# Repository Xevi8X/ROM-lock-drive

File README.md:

# ROM-lock-drive

This project is my intermediate engineering project (VI semester, Robotics, Faculty of Power and Aeronautical Engineering, WUT)

3D CAD models: https://grabcad.com/library/rom-lock-drive-1

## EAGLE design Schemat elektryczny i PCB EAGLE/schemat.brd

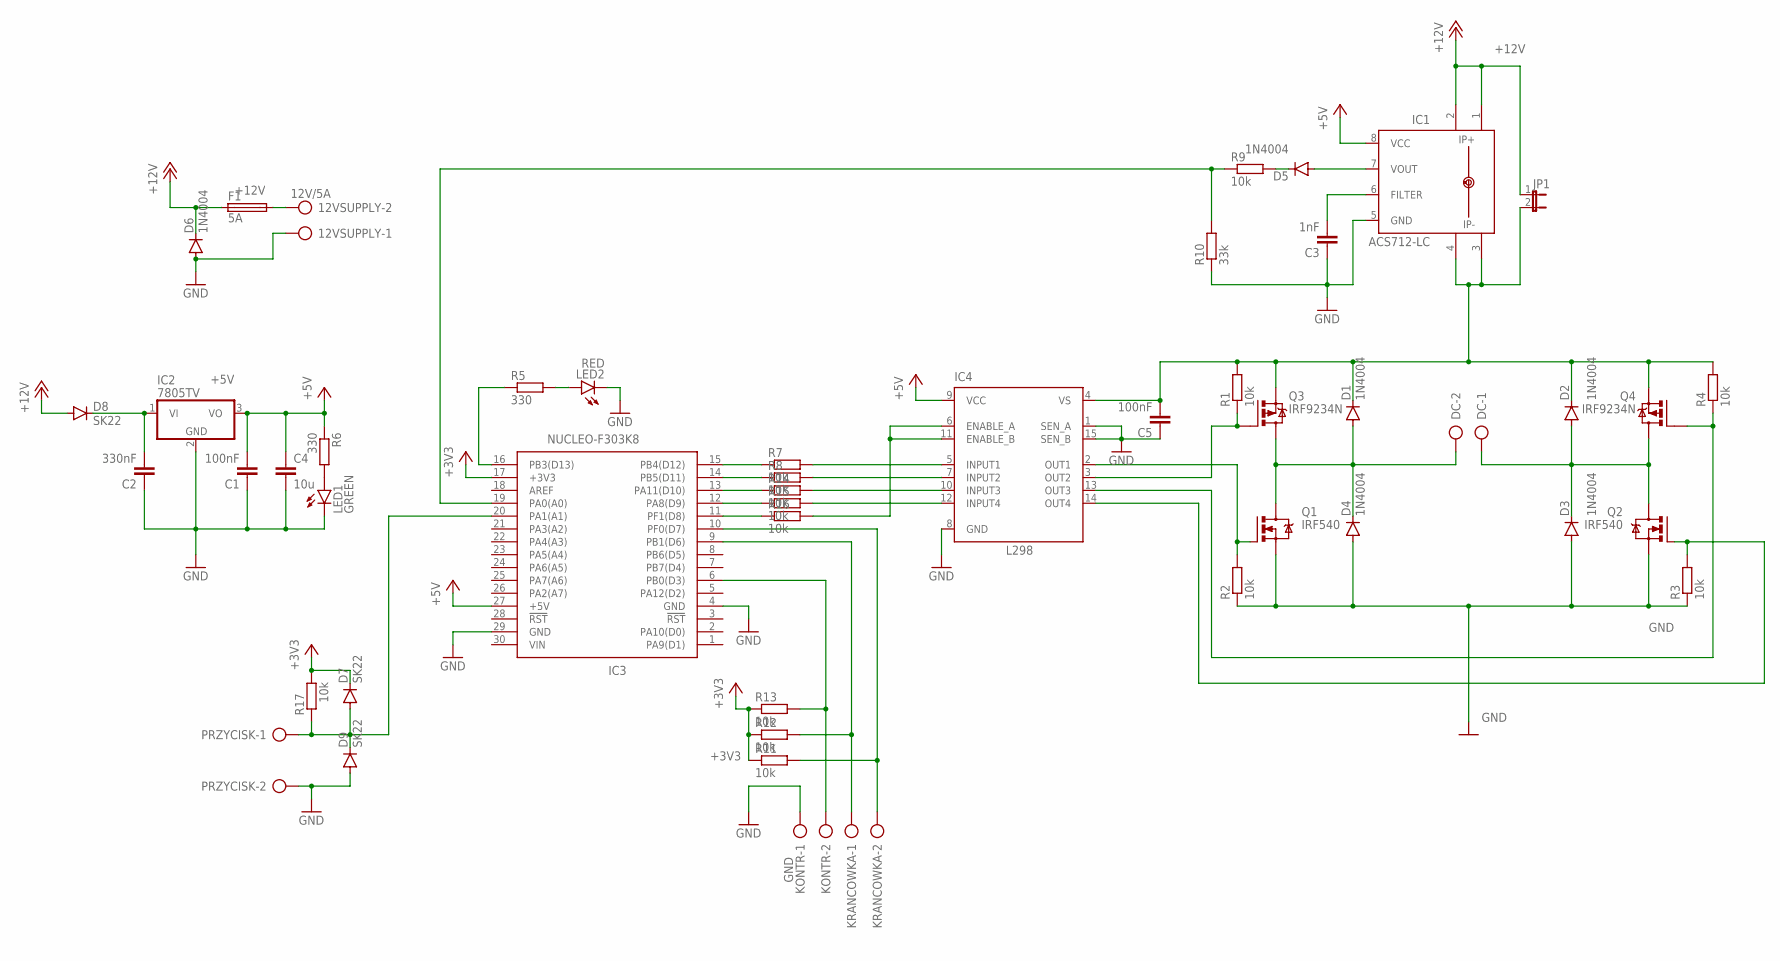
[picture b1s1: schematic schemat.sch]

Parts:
12VSUPPLY: 12V/5A; AK500/2-H
C1, C5: 100nF; C2.5-2
C2: 330nF; C2.5-2
C3: 1nF; C025-024X044
C4: 10u; C025-024X044
D1, D2, D3, D4, D5, D6: 1N4004; DO41-10
D7, D8, D9: SK22; SMB
DC: AK500/2-H
F1: 5A; TR5
IC1: ACS712-LC; SOIC8
IC2: 7805TV; TO220V
IC3: NUCLEO-F303K8; DIPS1524W66P254L5029H1500Q30N
IC4: L298; MULTIWATT-15
JP1: JP1E; JP1
KONTR: GND; AK500/2-H
KRANCOWKA: AK500/2-H
LED1: GREEN; LED3MM
LED2: RED; LED3MM
PRZYCISK: AK500/2-H
Q1, Q2: IRF540; TO220BV
Q3, Q4: IRF9234N; TO220BV
R1, R2, R3, R4, R7, R8, R9, R11, R12, R13, R14, R15, R16, R17: 10k; R1206
R5, R6: 330; R1206
R10: 33k; R1206

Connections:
+3V3: D7.C, IC3.17 (+3V3), R11.1, R12.1, R13.1, R17.2
+5V: C1.2, C4.1, IC1.8 (VCC), IC2.3 (VO), IC3.27 (+5V), IC4.9 (VCC), R6.1
+12V: D6.C, D8.A, F1.1, IC1.1 (IP+), IC1.2 (IP+1), JP1.1
GND: 12VSUPPLY.1, C1.1, C2.1, C3.1, C4.2, C5.1, D3.A, D4.A, D6.A, D9.A, IC1.5 (GND), IC2.2 (GND), IC3.4 (GND), IC3.29 (GND), IC4.1 (SEN_A), IC4.8 (GND), IC4.15 (SEN_B), KONTR.1, LED1.K (C), LED2.K (C), PRZYCISK.2, Q1.S, Q2.S, R2.1, R3.1, R10.1
unnamed: D2.A, D3.C, DC.1, Q2.D, Q4.D
unnamed: D1.A, D4.C, DC.2, Q1.D, Q3.D
unnamed: IC3.15 (PB4(D12)), R7.1
unnamed: IC4.5 (INPUT1), R7.2
unnamed: IC4.2 (OUT1), Q1.G, R2.2
unnamed: IC4.14 (OUT4), Q2.G, R3.2
unnamed: IC3.19 (PA0(A0)), R9.1, R10.2
unnamed: C2.2, D8.C, IC2.1 (VI)
unnamed: IC4.3 (OUT2), Q3.G, R1.1
unnamed: C5.2, D1.C, D2.C, IC1.3 (IP-), IC1.4 (IP-1), IC4.4 (VS), JP1.2, Q3.S, Q4.S, R1.2, R4.2
unnamed: IC4.13 (OUT3), Q4.G, R4.1
unnamed: D5.A, IC1.7 (VOUT)
unnamed: C3.2, IC1.6 (FILTER)
unnamed: D5.C, R9.2
unnamed: IC4.7 (INPUT2), R8.2
unnamed: IC3.14 (PB5(D11)), R8.1
unnamed: IC4.6 (ENABLE_A), IC4.11 (ENABLE_B), R16.2
unnamed: IC3.6 (PB0(D3)), KONTR.2, R13.2
unnamed: IC3.9 (PB1(D6)), KRANCOWKA.1, R12.2
unnamed: IC3.10 (PF0(D7)), KRANCOWKA.2, R11.2
unnamed: LED1.A, R6.2
unnamed: IC3.13 (PA11(D10)), R14.1
unnamed: IC4.10 (INPUT3), R14.2
unnamed: IC4.12 (INPUT4), R15.2
unnamed: IC3.12 (PA8(D9)), R15.1
unnamed: IC3.11 (PF1(D8)), R16.1
unnamed: IC3.16 (PB3(D13)), R5.1
unnamed: LED2.A, R5.2
unnamed: 12VSUPPLY.2, F1.2
unnamed: D7.A, D9.C, IC3.20 (PA1(A1)), PRZYCISK.1, R17.1

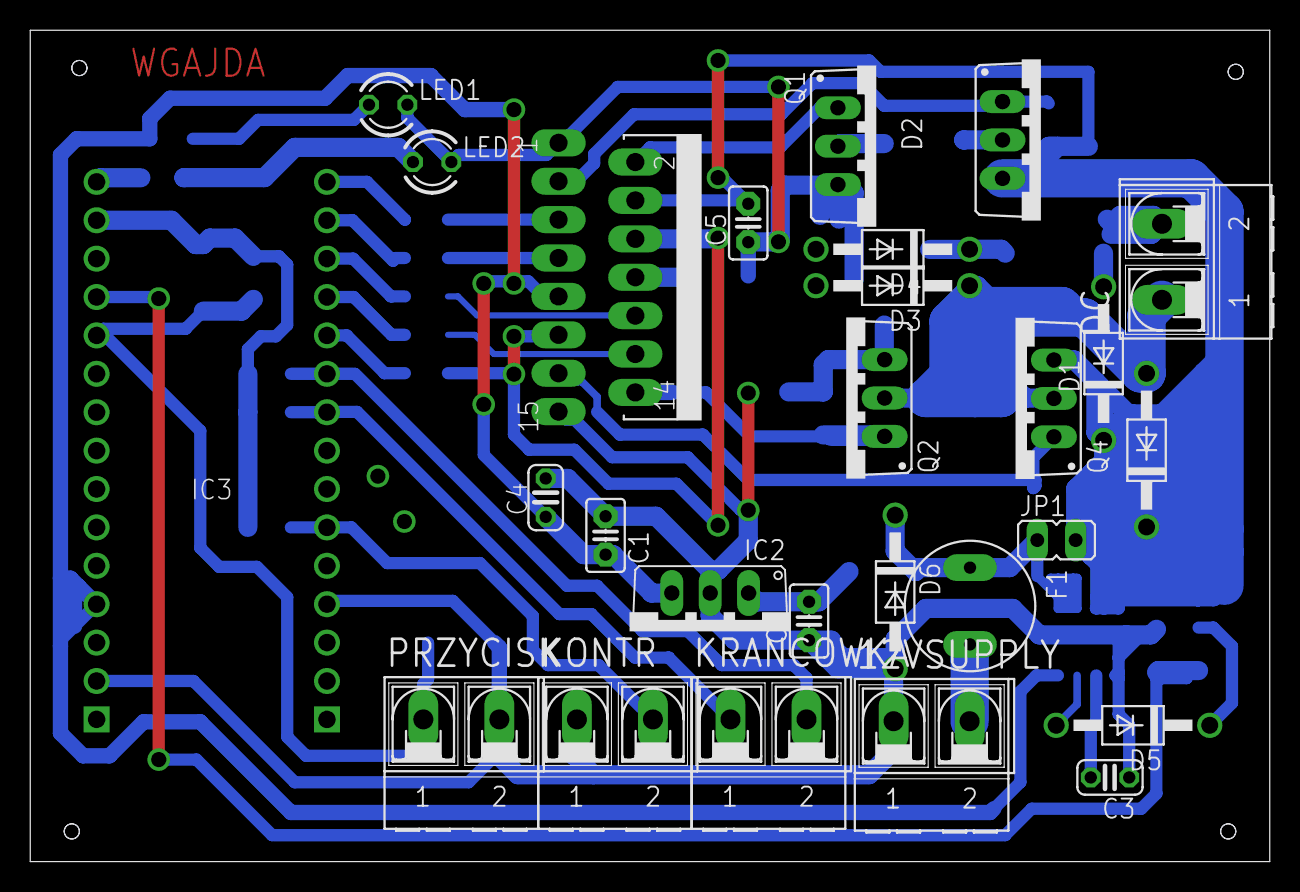
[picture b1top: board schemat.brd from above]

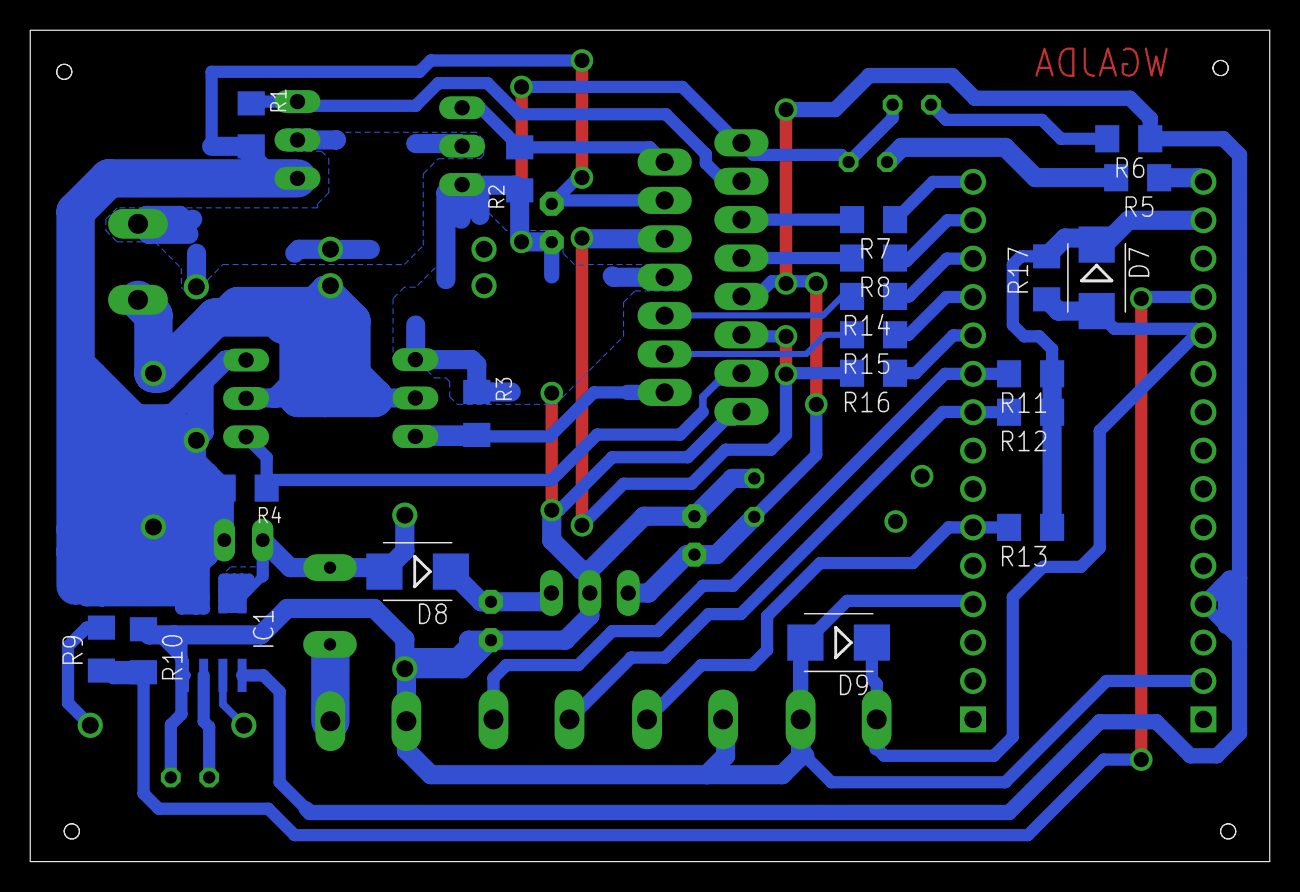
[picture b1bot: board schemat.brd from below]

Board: 2 copper layers, 82.0 x 55.0 mm, 48 parts (21 on the bottom side), 34 nets.

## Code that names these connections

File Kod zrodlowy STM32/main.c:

/**
  ******************************************************************************
  * @file    main.c
  * @author  Wojciech Gajda
  ******************************************************************************
*/


#include "stm32f3xx.h"
#include "stm32f3xx_nucleo_32.h"
			

uint16_t  PA1_Buff = 0x0000;
uint8_t   PA1_state = 0;
uint32_t  PF0_Buff = 0x0000;
uint8_t   PF0_state = 0;
uint32_t  PB1_Buff = 0x0000;
uint8_t   PB1_state = 0;
volatile int i= 0;
uint16_t  counter = 0;
uint16_t cc = 0;
//najmlodszy bit to update ogolny, drugi to update prompt
uint8_t update = 0x00;
uint8_t prompt = 0x00;


/*
uint8_t mosfetOn(uint8_t clockwise);
void mosfetOff();
void autoOff(int16_t delay_in_miliseconds);
void TIM2_IRQHandler(void);
void RRC_init();
void GPIO_init();
void TIM2_init();
*/


//Wylaczenie wszystkich kluczy w mostku H
void mosfetOff()
{
	counter = 0;
	GPIOB -> ODR |= GPIO_ODR_5;
	GPIOB -> ODR &= ~GPIO_ODR_4;
	GPIOA -> ODR |= GPIO_ODR_11;
	GPIOA -> ODR &= ~GPIO_ODR_8;

}

//Wlaczenie obrotow w odpowiednim kierunku, zwraca 1 gdy w momencie wywolania mostek byl w stanie innym niz mosfetOff()
uint8_t mosfetOn(uint8_t clockwise) //clockwise = 1, ccw = 0
{
	if((GPIOB -> ODR & GPIO_ODR_4 ) || (GPIOA -> ODR & GPIO_ODR_8) || !(GPIOB -> ODR & GPIO_ODR_5) || !(GPIOA -> ODR & GPIO_ODR_11) )
	{
		mosfetOff();
		return 1;
	}

	if(clockwise)
	{
		GPIOB -> BSRR |= GPIO_BSRR_BR_5;
		GPIOA -> BSRR |= GPIO_BSRR_BS_8;
	}
	else
	{
		GPIOA -> BSRR |= GPIO_BSRR_BR_11;
		GPIOB -> BSRR |= GPIO_BSRR_BS_4;
	}
	return 0;
}

//Sprawdzenie czy nie przekroczono limitu czasu
void autoOff(int16_t delay_in_miliseconds)
{
	if((GPIOB -> ODR & GPIO_ODR_4 ) || (GPIOA -> ODR & GPIO_ODR_8) || !(GPIOB -> ODR & GPIO_ODR_5) || !(GPIOA -> ODR & GPIO_ODR_11) )
			{
				counter++;
			}

			if(counter > delay_in_miliseconds)
			{
				mosfetOff();
			}
}

//Wyslanie komunikatu
void sendPrompt(uint8_t text)
{
	//przykladowo
	//0x01 jedno migniecie krotkie
	//0x07 jedno dlugie
	//0x55 4 krotkie
	//0x77 dwa dlugie
		update |= 0x02; //bit update prompt
		prompt = text;
}

//wyswietlenie promptu
void showPrompt()
{
	if(prompt == 0x00)
	{
		update &= ~0x02;
	}

	if((prompt & 0x01) == 0x01)
	{
		GPIOB->ODR |= GPIO_ODR_3;
	}
	else
	{
		GPIOB->ODR &= ~GPIO_ODR_3;
	}
		prompt >>= 1;
}


void TIM2_IRQHandler(void) //Wywolanie co 1ms
{
	if (0 != (TIM_SR_UIF & TIM2->SR)) // check update interrupt flag
	{
		TIM2->SR &= ~TIM_SR_UIF; // clear interrupt flag

		PA1_Buff <<=  1;
		PA1_Buff |= (GPIOA->IDR & GPIO_IDR_1)?(0x01):(0x00);
		PF0_Buff <<=  1;
		PF0_Buff |= (GPIOF->IDR & GPIO_IDR_0)?(0x01):(0x00);
		PB1_Buff <<= 1;
		PB1_Buff |= (GPIOB->IDR & GPIO_IDR_1)?(0x01):(0x00);

		update |=  0x01;
		autoOff(1000);
		cc++;
	}
}

//Inicjalizacja zegara HSI i lini zegarowych dla GPIO
void RRC_init()
{
	//--------------------------------------------------------------------------
		//URUCHOMIENIE ZEGARA HSI
		RCC->CR |= RCC_CR_HSION; //uruchomienie szybkiego zegara wewnetrznego 8MHz
		while (0 == (RCC->CR  & RCC_CR_HSIRDY)) {} //oczekiwanie na potwierdzenie uruchomienia
		RCC->CFGR |= RCC_CFGR_SW_0; //Przelaczenie sie na zegar HSI

		//--------------------------------------------------------------------------
		//URUCHOMIENIE PORTOW GPIO
		__HAL_RCC_GPIOA_CLK_ENABLE();
		__HAL_RCC_GPIOB_CLK_ENABLE();
		__HAL_RCC_GPIOC_CLK_ENABLE();
		__HAL_RCC_GPIOD_CLK_ENABLE();
		__HAL_RCC_GPIOF_CLK_ENABLE();

}
//Konfiguracja portów GPIO
void GPIO_init()
{


	//PF1 - Enable L298N
	GPIOF->MODER &= ~GPIO_MODER_MODER1_Msk;   //Bity Mode -> 00
	GPIOF->MODER |= GPIO_MODER_MODER1_0;     // Bity Mode -> 01 PP GP
	GPIOF->OSPEEDR &= ~GPIO_OSPEEDER_OSPEEDR1_Msk; //Low speed
	GPIOF->OTYPER &= ~GPIO_OTYPER_OT_1; //Push pull
	GPIOF->PUPDR &= ~GPIO_PUPDR_PUPDR1_Msk; //zadnych pull up/down
	GPIOF->ODR &= ~GPIO_ODR_1;		  //N-MOSFET, stan niski

	//Pull-up
	//PA1 - Przycisk
	GPIOA->MODER &= ~GPIO_MODER_MODER1_Msk; //Bity Mode -> 00 Input
	GPIOA->PUPDR &= ~GPIO_PUPDR_PUPDR1_Msk;
	GPIOA->PUPDR |= GPIO_PUPDR_PUPDR1_0; //Pull-up

	//PF0 - Krancowka 1
	GPIOF->MODER &= ~GPIO_MODER_MODER0_Msk; //Bity Mode -> 00 Input
	GPIOF->PUPDR &= ~GPIO_PUPDR_PUPDR0_Msk;
	GPIOF->PUPDR |= GPIO_PUPDR_PUPDR0_0; //Pull-up

	//PB1 - Krancowka 2
	GPIOB->MODER &= ~GPIO_MODER_MODER1_Msk; //Bity Mode -> 00 Input
	GPIOB->PUPDR &= ~GPIO_PUPDR_PUPDR1_Msk;
	GPIOB->PUPDR |= GPIO_PUPDR_PUPDR1_0; //Pull-up

	//PB0 - Kontrakton
	GPIOB->MODER &= ~GPIO_MODER_MODER0_Msk; //Bity Mode -> 00 Input
	GPIOB->PUPDR &= ~GPIO_PUPDR_PUPDR0_Msk;
	GPIOB->PUPDR |= GPIO_PUPDR_PUPDR0_0; //Pull-up

	//Push pull
	//PB5 - Mosfet Left-High
	GPIOB->MODER &= ~GPIO_MODER_MODER5_Msk;   //Bity Mode -> 00
	GPIOB->MODER |= GPIO_MODER_MODER5_0;     // Bity Mode -> 01 PP GP
	GPIOB->OSPEEDR &= ~GPIO_OSPEEDER_OSPEEDR5_Msk; //Low speed
	GPIOB->OTYPER &= ~GPIO_OTYPER_OT_5; //Push pull
	GPIOB->PUPDR &= ~GPIO_PUPDR_PUPDR5_Msk; //zadnych pull up/down
	GPIOB -> ODR |= GPIO_ODR_5;		  //P-MOSFET, stan wysoki

	//PB4 - Mosfet Left-Low
	GPIOB->MODER &= ~GPIO_MODER_MODER4_Msk;   //Bity Mode -> 00
	GPIOB->MODER |= GPIO_MODER_MODER4_0;     // Bity Mode -> 01 PP GP
	GPIOB->OSPEEDR &= ~GPIO_OSPEEDER_OSPEEDR4_Msk; //Low speed
	GPIOB->OTYPER &= ~GPIO_OTYPER_OT_4; //Push pull
	GPIOB->PUPDR &= ~GPIO_PUPDR_PUPDR4_Msk; //zadnych pull up/down
	GPIOB -> ODR &= ~GPIO_ODR_4;		  //N-MOSFET, stan niski

	//PA11 - Mosfet Right-High
	GPIOA->MODER &= ~GPIO_MODER_MODER11_Msk;   //Bity Mode -> 00
	GPIOA->MODER |= GPIO_MODER_MODER11_0;     // Bity Mode -> 01 PP GP
	GPIOA->OSPEEDR &= ~GPIO_OSPEEDER_OSPEEDR11_Msk; //Low speed
	GPIOA->OTYPER &= ~GPIO_OTYPER_OT_11; //Push pull
	GPIOA->PUPDR &= ~GPIO_PUPDR_PUPDR11_Msk; //zadnych pull up/down
	GPIOA -> ODR |= GPIO_ODR_11;		  //P-MOSFET, stan wysoki

	//PA8 - Mosfet Right-Low
	GPIOA->MODER &= ~GPIO_MODER_MODER8_Msk;   //Bity Mode -> 00
	GPIOA->MODER |= GPIO_MODER_MODER8_0;     // Bity Mode -> 01 PP GP
	GPIOA->OSPEEDR &= ~GPIO_OSPEEDER_OSPEEDR8_Msk; //Low speed
	GPIOA->OTYPER &= ~GPIO_OTYPER_OT_8; //Push pull
	GPIOA->PUPDR &= ~GPIO_PUPDR_PUPDR8_Msk; //zadnych pull up/down
	GPIOA -> ODR &= ~GPIO_ODR_8;		  //N-MOSFET, stan niski

	//PB3 - Dioda
	GPIOB->MODER &= ~GPIO_MODER_MODER3_Msk;   //Bity Mode -> 00
	GPIOB->MODER |= GPIO_MODER_MODER3_0;     // Bity Mode -> 01 PP GP
	GPIOB->OSPEEDR &= ~GPIO_OSPEEDER_OSPEEDR3_Msk; //Low speed
	GPIOB->OTYPER &= ~GPIO_OTYPER_OT_3; //Push pull
	GPIOB->PUPDR &= ~GPIO_PUPDR_PUPDR1_Msk; //zadnych pull up/down
	GPIOB->ODR &= ~GPIO_ODR_3;		  //domyslnie enable

	GPIOF->ODR |= GPIO_ODR_1;
}

//Konf. timera
void TIM2_init()
{
	//--------------------------------------------------------------------------
		//KONFIGURACJA TIMERA TIM2 - przerwanie co 1ms
		RCC->APB1ENR |= RCC_APB1ENR_TIM2EN; //uruchomienie linii zegarowej
		//8,000,000Hz / 1000Hz = 8000, 8000/800 = 10
		TIM2->PSC = 64 - 1; //konfiguracja prescalera  w zakresie od 0 do 65535 + 1
		TIM2->ARR = 125 - 1; //i rejestru autoreload
		TIM2->DIER |= TIM_DIER_UIE; //uruchomienie update interrupt
		//Zostawiamy na frozen, nie bedziemy korzystac z funkcjonalnosci PWM
		TIM2->CCMR1 &= ~TIM_CCMR1_OC1M_Msk;

		//--------------------------------------------------------------------------
		//URUCHOMINIE MODULU PRZERWAN NVIC DLA TIM2
		NVIC_EnableIRQ(TIM2_IRQn);

		//--------------------------------------------------------------------------
		//URUCHOMINIE TIM2
		TIM2->CR1 |= TIM_CR1_CEN;

		//Komunikat o poprawnej inicjalizacji
		sendPrompt(0x15); // 3 krotkie
}


int main(void)
{

 	RRC_init();
	GPIO_init();
	TIM2_init();

	for(;;)
	{
		if((update & 0x01) == 0x01)
		{
			__disable_irq();
			if((PA1_Buff == 0xFFFF) && PA1_state == 0)
			{
				PA1_state = 1;
			}

			if((PA1_Buff == 0x0000) && PA1_state == 1)
			{
				PA1_state = 0;
				if((GPIOB->IDR & GPIO_IDR_0 ) == 0)
				{
					if((GPIOF->IDR & GPIO_IDR_0) == 0)
					{
					sendPrompt(0x01);
					mosfetOn(0);
					}
					else
					{
					sendPrompt(0x05);
					mosfetOn(1);
					}
				}
				else
				{
					sendPrompt(0xE7);
					mosfetOn(1);
				}
			}

			if((PF0_Buff == 0xFFFFFFFF) && PF0_state == 0)
			{
				PF0_state = 1;
			}

			if((PF0_Buff == 0x00000000) && PF0_state == 1)
			{
				PF0_state = 0;
				counter = 800;
			}

			if((PB1_Buff == 0xFFFFFFFF) && PB1_state == 0)
			{
				PB1_state = 1;
			}

			if((PB1_Buff == 0x00000000) && PB1_state == 1)
			{
				PB1_state = 0;
				counter = 800;
			}

			if(cc > 200)
			{
				if((update & 0x02) == 0x02)
				{
					showPrompt();
				}
				cc = 0;
			}

			update &= ~0x01;
			__enable_irq();
		}
	}
}

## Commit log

2023-01-14 init
